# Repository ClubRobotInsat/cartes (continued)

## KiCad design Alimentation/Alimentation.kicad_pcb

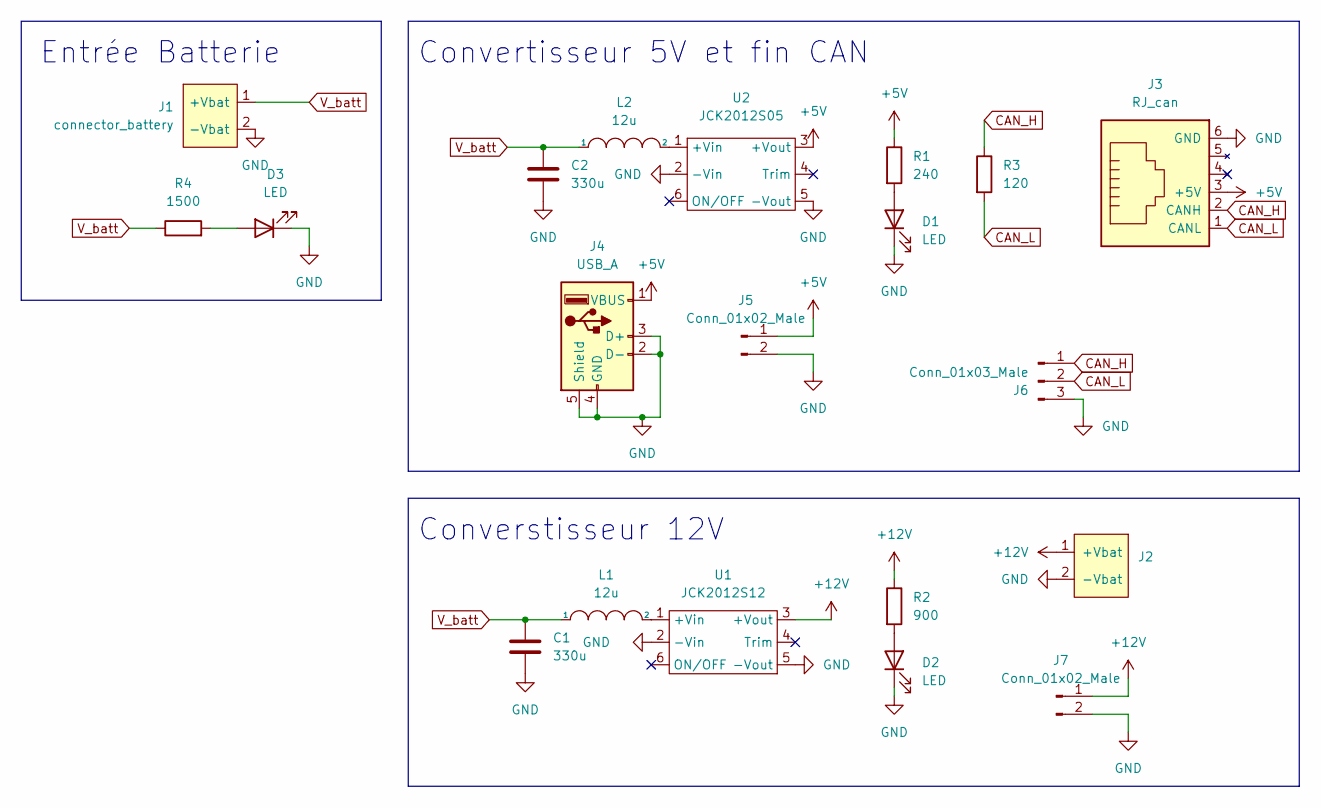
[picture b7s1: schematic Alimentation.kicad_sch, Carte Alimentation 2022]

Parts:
C1, C2: 330u; CP_Radial_D7.5mm_P2.50mm
D1, D2, D3: LED; LED_D5.0mm
J1: connector_battery; WR_TBL_3137_2pins
J2: WR_TBL_3137_2pins
J3: RJ_can; RJ12
J4: USB_A
J5, J7: Conn_01x02_Male; PinHeader_1x02_P2.54mm_Horizontal
J6: Conn_01x03_Male; PinHeader_1x03_P2.54mm_Horizontal
L1, L2: 12u; L_Radial_D7.8mm_P5.00mm_Fastron_07HCP
R1: 240; R_0805_2012Metric_Pad1.20x1.40mm_HandSolder
R2: 900; R_0805_2012Metric_Pad1.20x1.40mm_HandSolder
R3: 120; R_0805_2012Metric_Pad1.20x1.40mm_HandSolder
R4: 1500; R_0805_2012Metric_Pad1.20x1.40mm_HandSolder
U1: JCK2012S12; JCK
U2: JCK2012S05; JCK

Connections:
+5V: J3.3 (+5V), J4.1 (VBUS), J5.1, R1.1, U2.3 (+Vout)
+12V: J2.1 (+Vbat), J7.1, R2.1, U1.3 (+Vout)
CAN_H: J3.2 (CANH), J6.1, R3.1
CAN_L: J3.1 (CANL), J6.2, R3.2
GND: C1.2, C2.2, D1.1 (K), D2.1 (K), D3.1 (K), J1.2 (-Vbat), J2.2 (-Vbat), J3.6 (GND), J4.2 (D-), J4.3 (D+), J4.4 (GND), J4.5 (Shield), J5.2, J6.3, J7.2, U1.2 (-Vin), U1.5 (-Vout), U2.2 (-Vin), U2.5 (-Vout)
unnamed: D1.2 (A), R1.2
unnamed: D2.2 (A), R2.2
unnamed: D3.2 (A), R4.2
unnamed: L1.2, U1.1 (+Vin)
unnamed: L2.2, U2.1 (+Vin)
V_batt: C1.1, C2.1, J1.1 (+Vbat), L1.1, L2.1, R4.1

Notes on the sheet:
Convertisseur 5V et fin CAN
Converstisseur 12V
Entrée Batterie

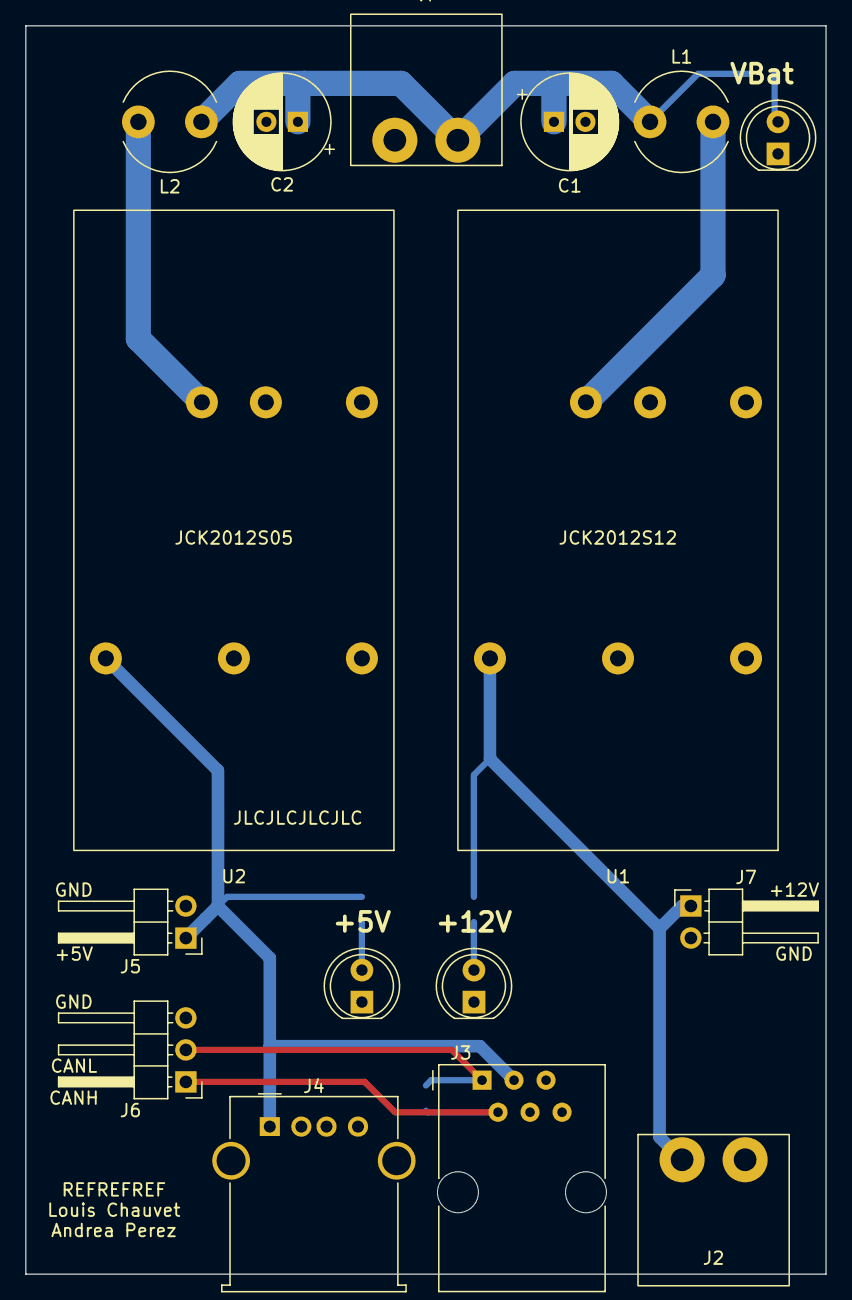
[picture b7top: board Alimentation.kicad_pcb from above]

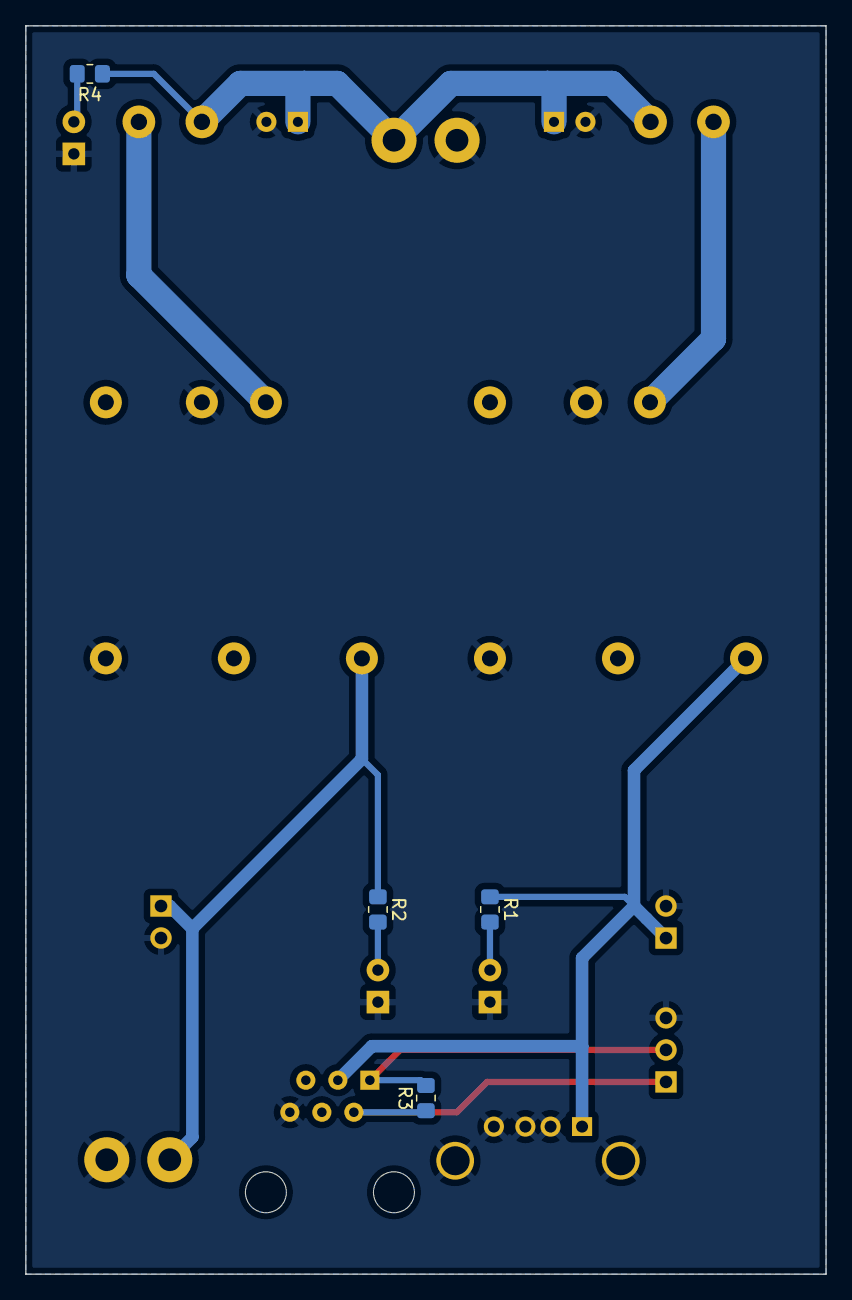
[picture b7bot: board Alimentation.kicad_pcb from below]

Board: 2 copper layers, 63.5 x 99.1 mm, 20 parts (4 on the bottom side), 11 nets.

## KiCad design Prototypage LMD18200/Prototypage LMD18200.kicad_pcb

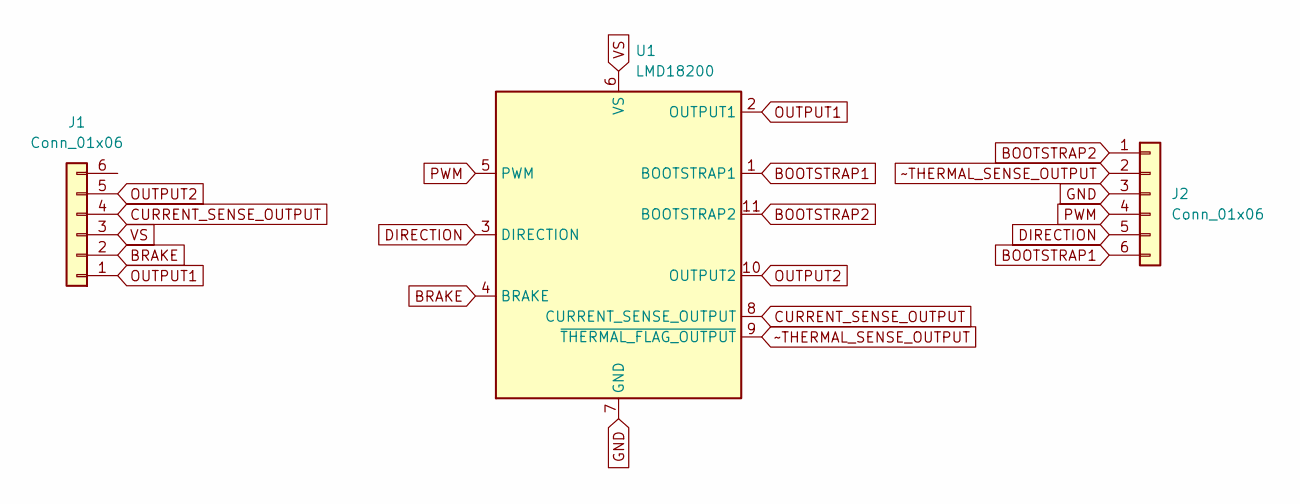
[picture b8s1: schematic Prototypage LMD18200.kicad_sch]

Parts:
J1, J2: Conn_01x06; PinHeader_1x06_P2.54mm_Vertical
U1: LMD18200; TO-220-11_P3.4x5.08mm_StaggerOdd_Lead4.85mm_Vertical

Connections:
BOOTSTRAP1: J2.6, U1.1 (BOOTSTRAP1)
BOOTSTRAP2: J2.1, U1.11 (BOOTSTRAP2)
BRAKE: J1.2, U1.4 (BRAKE)
CURRENT_SENSE_OUTPUT: J1.4, U1.8 (CURRENT_SENSE_OUTPUT)
DIRECTION: J2.5, U1.3 (DIRECTION)
GND: J2.3, U1.7 (GND)
OUTPUT1: J1.1, U1.2 (OUTPUT1)
OUTPUT2: J1.5, U1.10 (OUTPUT2)
PWM: J2.4, U1.5 (PWM)
VS: J1.3, U1.6 (VS)
~THERMAL_SENSE_OUTPUT: J2.2, U1.9 (~THERMAL_FLAG_OUTPUT)

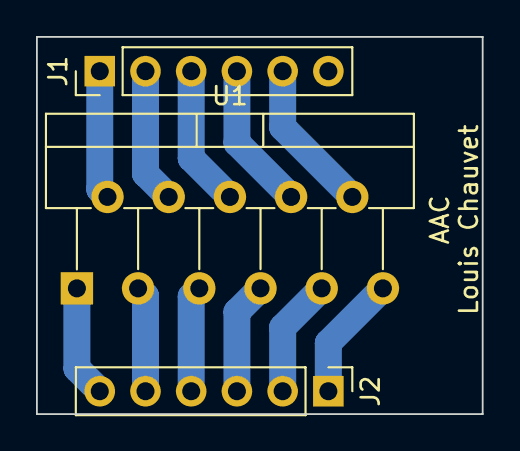
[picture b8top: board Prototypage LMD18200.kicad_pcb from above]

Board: 2 copper layers, 24.8 x 21.0 mm, 3 parts (0 on the bottom side), 11 nets.

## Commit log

2022-07-20 Ajout de la led
2022-07-23 Update alimentation; Add Base roulante
2022-07-24 Update base roulante
2022-07-25 Commande
2022-08-30 Update gitignore
2022-08-30 Update card to cut board near to the connector
2022-12-08 Add Base roulante updated
2023-02-16 Avant de partir je donne tout
2023-03-25 Ajout de la première version du hat
2023-05-11 rjcan split
2023-05-11 base roulante reroute au cas ou
2023-05-11 Modifs proposés par Liam
    J'ai enleve un via et j'ai rajouter du texte sur la carte, il manque juste une reference avec NOM#Num
2023-05-11 carte IO
2023-05-11 Modifications apportées aux dernières cartes
2023-05-11 Modif de la carteIO
2023-05-12 added some vias for the grownd plain
2023-10-09 Fichiers de la base roulante pour 2024
2023-10-09 Mise à jour du schema pour inclure certains blocs
2023-10-14 J'ai changé la carte Base Roulante pour n'avoir qu'un driver et des interfaces
2023-11-09 Update Base_Roulante_2024
2023-11-12 Added the schematic with use of hierachy
    Top_level_schematic is the "main" schematic, with stepper_motor_driver as a sub-schematic. Both need to be in the same folder to work.
2023-12-21 Created folder for the H bridge motor driver schematics
2023-12-21 Added top level schematic and H bridge schematic.
    Top level schematic is the main schematic, the other files contain the required schematics for using hierarchical sheets.
